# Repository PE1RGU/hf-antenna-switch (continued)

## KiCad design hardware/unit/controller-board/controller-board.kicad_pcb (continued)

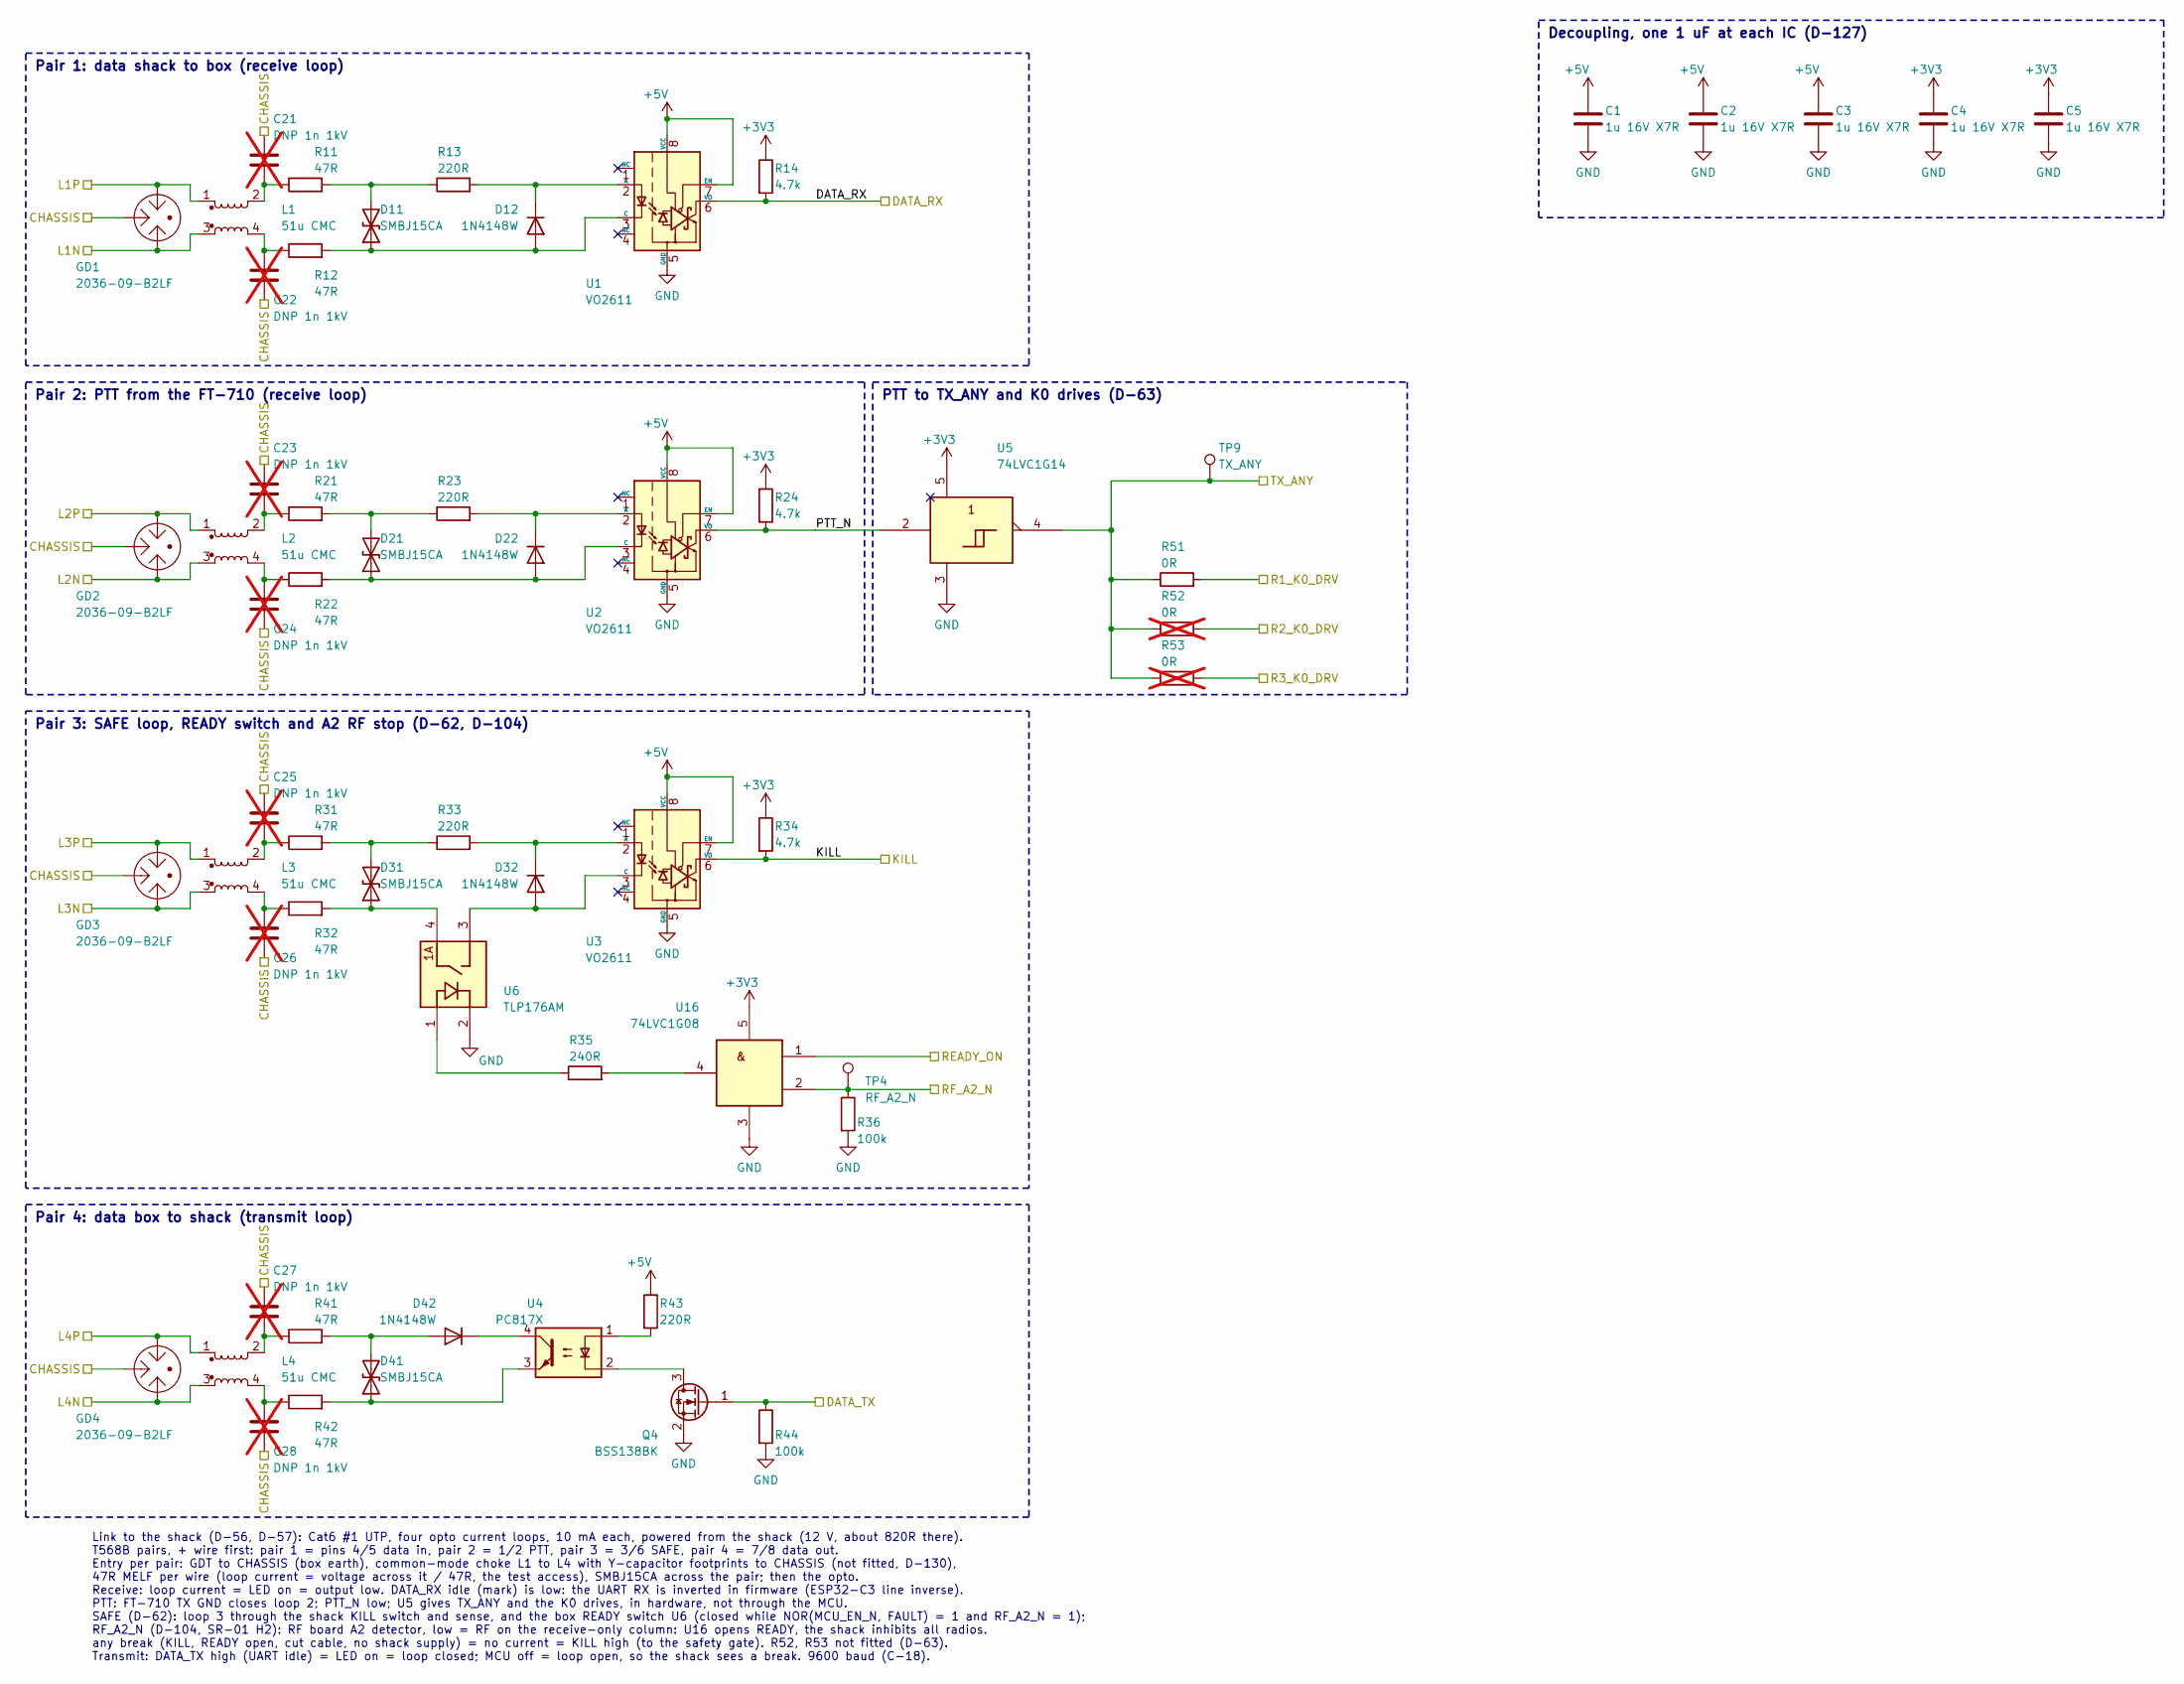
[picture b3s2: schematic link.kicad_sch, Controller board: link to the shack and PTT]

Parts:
C1, C2, C3, C4, C5: 1u 16V X7R; C_0603_1608Metric_Pad1.08x0.95mm_HandSolder
C21, C22, C23, C24, C25, C26, C27, C28: DNP 1n 1kV; C_1206_3216Metric_Pad1.33x1.80mm_HandSolder; not fitted
D11, D21, D31, D41: SMBJ15CA; D_SMB; MPN SMBJ15CA
D12, D22, D32, D42: 1N4148W; D_SOD-123; MPN 1N4148W
GD1, GD2, GD3, GD4: 2036-09-B2LF; GDT_3Pin_P4.40mm_Bourns-2036-B2_Littelfuse-SL1003A-R; MPN 2036-09-B2LF
L1, L2, L3, L4: 51u CMC; L_CMC_TDK_ACT45B; MPN ACT45B-510-2P-TL003
Q4: BSS138BK; SOT-23; MPN BSS138BK
R11, R12, R21, R22, R31, R32, R41, R42: 47R; R_MELF_MMB-0207
R13, R23, R33: 220R; R_MiniMELF_MMA-0204
R14, R24, R34: 4.7k; R_0603_1608Metric_Pad0.98x0.95mm_HandSolder
R35: 240R; R_0603_1608Metric_Pad0.98x0.95mm_HandSolder
R36, R44: 100k; R_0603_1608Metric_Pad0.98x0.95mm_HandSolder
R43: 220R; R_0603_1608Metric_Pad0.98x0.95mm_HandSolder
R51: 0R; R_0603_1608Metric_Pad0.98x0.95mm_HandSolder
R52, R53: 0R; R_0603_1608Metric_Pad0.98x0.95mm_HandSolder; not fitted
TP4: RF_A2_N; TestPoint_Pad_D1.5mm
TP9: TX_ANY; TestPoint_Pad_D1.5mm
U1, U2, U3: VO2611; DIP-8_W7.62mm; MPN VO2611
U4: PC817X; DIP-4_W7.62mm; MPN PC817X2NSZ9F
U5: 74LVC1G14; SOT-23-5; MPN 74LVC1G14GV
U6: TLP176AM; SOP-4_P2.54mm_PhotoRelay_LongPad; MPN TLP176AM(TPL,E)
U16: 74LVC1G08; SOT-23-5; MPN 74LVC1G08GV

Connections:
+3V3: C4.1, C5.1, R14.1, R24.1, R34.1, U5.5, U16.5; also elsewhere on the board
+5V: C1.1, C2.1, C3.1, R43.1, U1.7 (EN), U1.8 (VCC), U2.7 (EN), U2.8 (VCC), U3.7 (EN), U3.8 (VCC); also elsewhere on the board
/Link and PTT/CHASSIS: C21.1, C22.2, C23.1, C24.2, C25.1, C26.2, C27.1, C28.2, GD1.2, GD2.2, GD3.2, GD4.2; also elsewhere on the board
/Link and PTT/DATA_RX: R14.2, U1.6 (VO); also elsewhere on the board
/Link and PTT/KILL: R34.2, U3.6 (VO); also elsewhere on the board
/Link and PTT/L1N: GD1.1, L1.3; also elsewhere on the board
/Link and PTT/L1P: GD1.3, L1.1; also elsewhere on the board
/Link and PTT/L2N: GD2.1, L2.3; also elsewhere on the board
/Link and PTT/L2P: GD2.3, L2.1; also elsewhere on the board
/Link and PTT/L3N: GD3.1, L3.3; also elsewhere on the board
/Link and PTT/L3P: GD3.3, L3.1; also elsewhere on the board
/Link and PTT/L4N: GD4.1, L4.3; also elsewhere on the board
/Link and PTT/L4P: GD4.3, L4.1; also elsewhere on the board
/Link and PTT/PTT_N: R24.2, U2.6 (VO), U5.2
/Link and PTT/R1_K0_DRV: R51.2; also elsewhere on the board
/Link and PTT/R2_K0_DRV: R52.2; also elsewhere on the board
/Link and PTT/R3_K0_DRV: R53.2; also elsewhere on the board
/Link and PTT/READY_ON: U16.1; also elsewhere on the board
/Link and PTT/RF_A2_N: R36.1, TP4.1, U16.2; also elsewhere on the board
/Link and PTT/TX_ANY: R51.1, R52.1, R53.1, TP9.1, U5.4; also elsewhere on the board
/MCU and safety gate/DATA_TX: Q4.1 (G), R44.1; also elsewhere on the board
GND: C1.2, C2.2, C3.2, C4.2, C5.2, Q4.2 (S), R36.2, R44.2, U1.5 (GND), U2.5 (GND), U3.5 (GND), U5.3, U6.2, U16.3; also elsewhere on the board
unnamed: C21.2, L1.2, R11.1
unnamed: C22.1, L1.4, R12.1
unnamed: C23.2, L2.2, R21.1
unnamed: C24.1, L2.4, R22.1
unnamed: C25.2, L3.2, R31.1
unnamed: C26.1, L3.4, R32.1
unnamed: C27.2, L4.2, R41.1
unnamed: C28.1, L4.4, R42.1
unnamed: D11.1 (A1), D12.2 (A), R12.2, U1.3 (C)
unnamed: D11.2 (A2), R11.2, R13.1
unnamed: D12.1 (K), R13.2, U1.2 (A)
unnamed: D21.1 (A1), D22.2 (A), R22.2, U2.3 (C)
unnamed: D21.2 (A2), R21.2, R23.1
unnamed: D22.1 (K), R23.2, U2.2 (A)
unnamed: D31.1 (A1), R32.2, U6.4
unnamed: D31.2 (A2), R31.2, R33.1
unnamed: D32.2 (A), U3.3 (C), U6.3
unnamed: D32.1 (K), R33.2, U3.2 (A)
unnamed: D41.1 (A1), R42.2, U4.3
unnamed: D41.2 (A2), D42.2 (A), R41.2
unnamed: D42.1 (K), U4.4
unnamed: Q4.3 (D), U4.2
unnamed: R35.1, U6.1
unnamed: R35.2, U16.4
unnamed: R43.2, U4.1

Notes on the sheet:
Link to the shack (D-56, D-57): Cat6 #1 UTP, four opto current loops, 10 mA each, powered from the shack (12 V, about 820R there). T568B pairs, + wire first: pair 1 = pins 4/5 data in, pair 2 = 1/2 PTT, pair 3 = 3/6 SAFE, pair 4 = 7/8 data out. Entry per pair: GDT to CHASSIS (box earth), common-mod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
Pair 1: data shack to box (receive loop)
Pair 2: PTT from the FT-710 (receive loop)
PTT to TX_ANY and K0 drives (D-63)
Pair 3: SAFE loop, READY switch and A2 RF stop (D-62, D-104)
Pair 4: data box to shack (transmit loop)
Decoupling, one 1 uF at each IC (D-127)

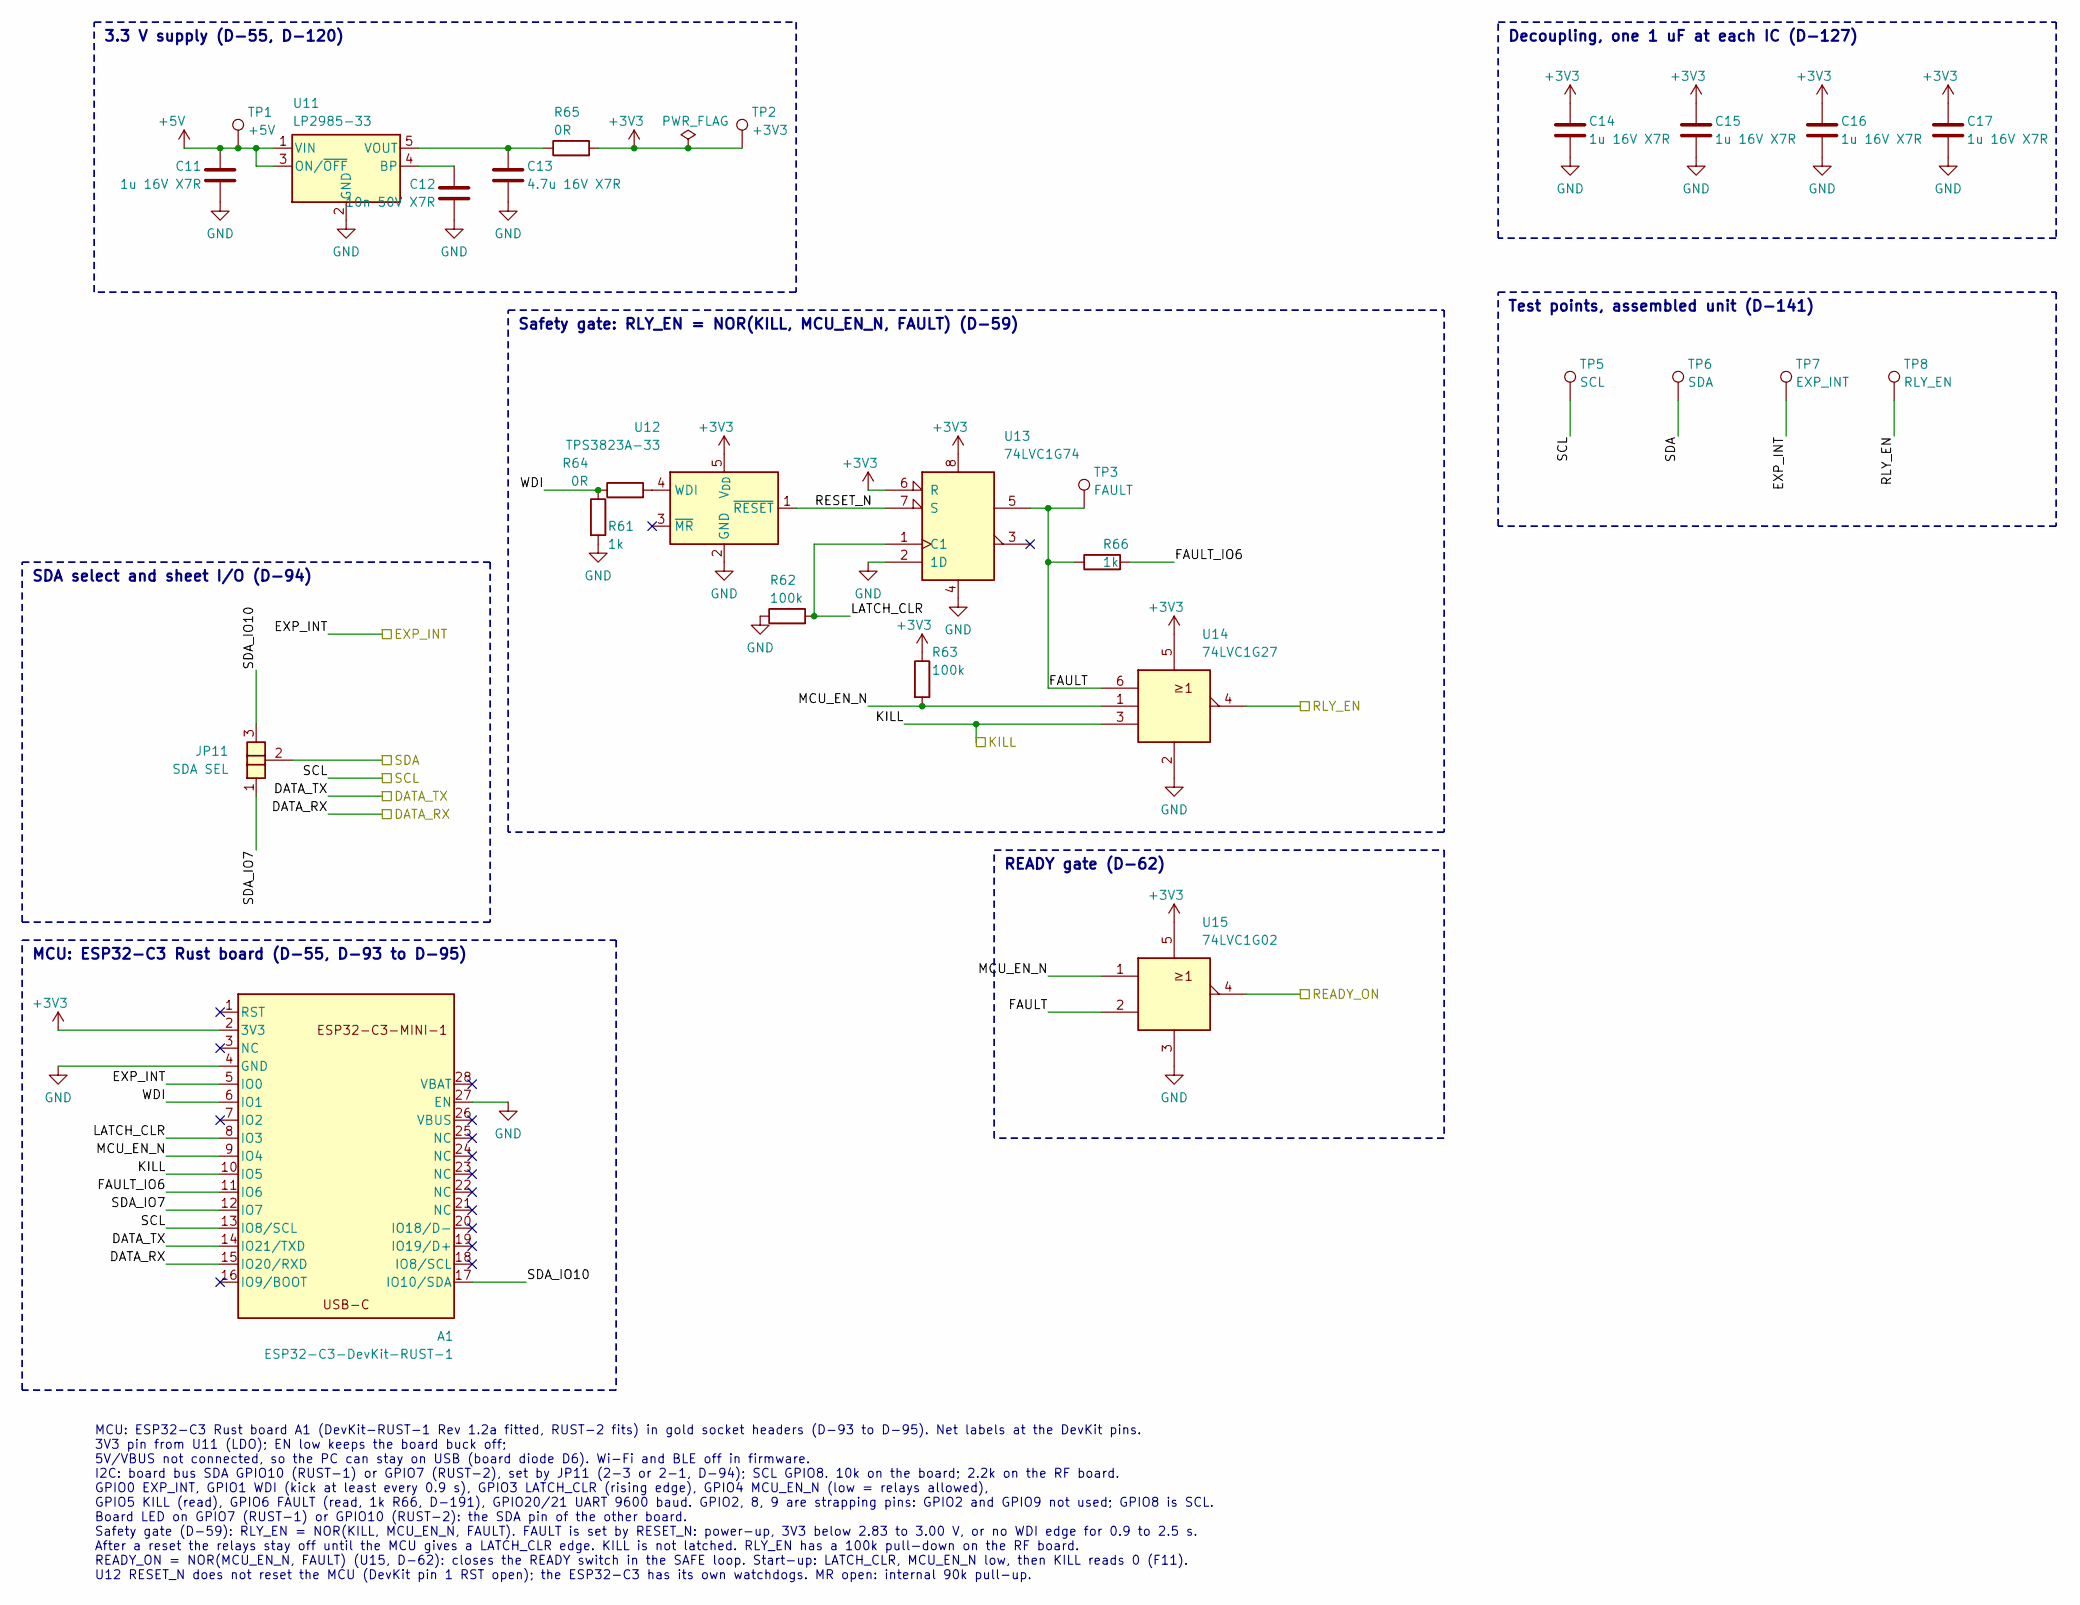
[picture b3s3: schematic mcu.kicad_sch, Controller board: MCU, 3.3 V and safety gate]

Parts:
A1: ESP32-C3-DevKit-RUST-1; ESP32-C3-DevKit-RUST_Socket
C11, C14, C15, C16, C17: 1u 16V X7R; C_0603_1608Metric_Pad1.08x0.95mm_HandSolder
C12: 10n 50V X7R; C_0603_1608Metric_Pad1.08x0.95mm_HandSolder
C13: 4.7u 16V X7R; C_0805_2012Metric_Pad1.18x1.45mm_HandSolder
JP11: SDA SEL; SolderJumper-3_P1.3mm_Open_RoundedPad1.0x1.5mm_NumberLabels
R61, R66: 1k; R_0603_1608Metric_Pad0.98x0.95mm_HandSolder
R62, R63: 100k; R_0603_1608Metric_Pad0.98x0.95mm_HandSolder
R64: 0R; R_0603_1608Metric_Pad0.98x0.95mm_HandSolder
R65: 0R; R_1206_3216Metric_Pad1.30x1.75mm_HandSolder
TP1: +5V; TestPoint_Pad_D1.5mm
TP2: +3V3; TestPoint_Pad_D1.5mm
TP3: FAULT; TestPoint_Pad_D1.5mm
TP5: SCL; TestPoint_Pad_D1.5mm
TP6: SDA; TestPoint_Pad_D1.5mm
TP7: EXP_INT; TestPoint_Pad_D1.5mm
TP8: RLY_EN; TestPoint_Pad_D1.5mm
U11: LP2985-33; SOT-23-5; MPN LP2985-33DBVR
U12: TPS3823A-33; SOT-23-5; MPN TPS3823A-33DBVR
U13: 74LVC1G74; VSSOP-8_2.3x2mm_P0.5mm; MPN SN74LVC1G74DCUR
U14: 74LVC1G27; SOT-23-6; MPN SN74LVC1G27DBVR
U15: 74LVC1G02; SOT-23-5; MPN 74LVC1G02GV

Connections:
+3V3: A1.2 (3V3), C14.1, C15.1, C16.1, C17.1, R63.1, R65.2, TP2.1, U12.5 (V_{DD}), U13.6 (R), U13.8, U14.5, U15.5; also elsewhere on the board
+5V: C11.1, TP1.1, U11.1 (VIN), U11.3 (ON/~OFF); also elsewhere on the board
/Link and PTT/DATA_RX: A1.15 (IO20/RXD); also elsewhere on the board
/Link and PTT/KILL: A1.10 (IO5), U14.3; also elsewhere on the board
/Link and PTT/READY_ON: U15.4; also elsewhere on the board
/MCU and safety gate/DATA_TX: A1.14 (IO21/TXD); also elsewhere on the board
/MCU and safety gate/EXP_INT: A1.5 (IO0), TP7.1; also elsewhere on the board
/MCU and safety gate/FAULT: R66.1, TP3.1, U13.5, U14.6, U15.2
/MCU and safety gate/FAULT_IO6: A1.11 (IO6), R66.2
/MCU and safety gate/LATCH_CLR: A1.8 (IO3), R62.2, U13.1 (C1)
/MCU and safety gate/MCU_EN_N: A1.9 (IO4), R63.2, U14.1, U15.1
/MCU and safety gate/RESET_N: U12.1 (~RESET), U13.7 (S)
/MCU and safety gate/RLY_EN: TP8.1, U14.4; also elsewhere on the board
/MCU and safety gate/SCL: A1.13 (IO8/SCL), TP5.1; also elsewhere on the board
/MCU and safety gate/SDA: JP11.2, TP6.1; also elsewhere on the board
/MCU and safety gate/WDI: A1.6 (IO1), R61.1, R64.1
GND: A1.4 (GND), A1.27 (EN), C11.2, C12.2, C13.2, C14.2, C15.2, C16.2, C17.2, R61.2, R62.1, U11.2 (GND), U12.2 (GND), U13.2 (1D), U13.4, U14.2, U15.3; also elsewhere on the board
unnamed: C12.1, U11.4 (BP)
unnamed: C13.1, R65.1, U11.5 (VOUT)
unnamed: R64.2, U12.4 (WDI)

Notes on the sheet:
MCU: ESP32-C3 Rust board A1 (DevKit-RUST-1 Rev 1.2a fitted, RUST-2 fits) in gold socket headers (D-93 to D-95). Net labels at the DevKit pins. 3V3 pin from U11 (LDO); EN low keeps the board buck off; 5V/VBUS not connected, so the PC can stay on USB (board diode D6). Wi-Fi and BLE off in firmware. I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
3.3 V supply (D-55, D-120)
SDA select and sheet I/O (D-94)
MCU: ESP32-C3 Rust board (D-55, D-93 to D-95)
Safety gate: RLY_EN = NOR(KILL, MCU_EN_N, FAULT) (D-59)
READY gate (D-62)
Decoupling, one 1 uF at each IC (D-127)
Test points, assembled unit (D-141)

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
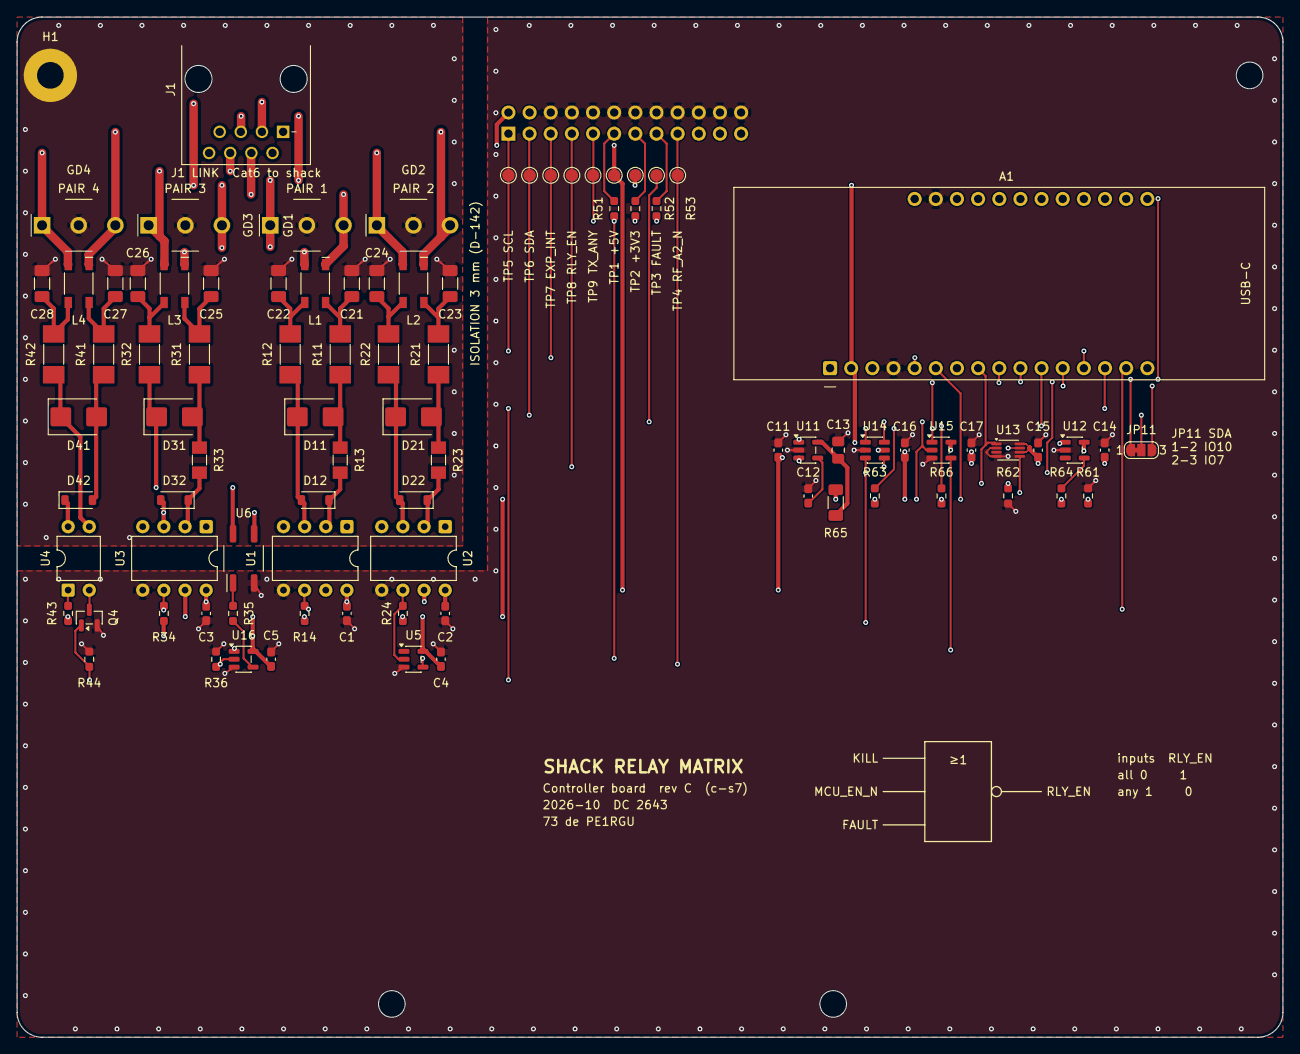
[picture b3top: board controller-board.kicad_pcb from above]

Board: 4 copper layers, 152.0 x 122.5 mm, 93 parts (1 on the bottom side), 62 nets.

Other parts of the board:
H2, H3, H4: M3 NPTH; MountingHole_3.2mm_M3

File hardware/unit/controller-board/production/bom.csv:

Designator,Footprint,Quantity,Value,LCSC Part #
A1,ESP32-C3-DevKit-RUST_Socket,1,ESP32-C3-DevKit-RUST-1,
"C1, C11, C14, C15, C16, C17, C2, C3, C4, C5",0603,10,1u 16V X7R,
C12,0603,1,10n,
C13,0805,1,4.7u 16V X7R,
"D11, D21, D31, D41",D_SMB,4,SMBJ15CA,
"D12, D22, D32, D42",D_SOD-123,4,1N4148W,
"GD1, GD2, GD3, GD4",GDT_3Pin_P4.40mm_Bourns-2036-B2_Littelfuse-SL1003A-R,4,2036-09-B2LF,
J1,RJ45_8P8C_Unshielded_TabDown,1,RJ45 LINK,
J2,PinSocket_2x12_P2.54mm_Vertical,1,to RF board J14,
JP11,SolderJumper-3_P1.3mm_Open_RoundedPad1.0x1.5mm_NumberLabels,1,SDA SEL,
"L1, L2, L3, L4",L_CMC_TDK_ACT45B,4,51u CMC,
Q4,SOT-23,1,BSS138BK,
"R11, R12, R21, R22, R31, R32, R41, R42",R_MELF_MMB-0207,8,47R,
"R13, R23, R33",R_MiniMELF_MMA-0204,3,220R,
"R14, R24, R34",0603,3,4.7k,
R35,0603,1,240R,
"R36, R44, R62, R63",0603,4,100k,
R43,0603,1,220R,
"R51, R64",0603,2,0R,
R61,0603,1,1k,
R65,1206,1,0R,
"U1, U2, U3",DIP-8_W7.62mm,3,VO2611,
U11,SOT-23-5,1,LP2985-33,
U12,SOT-23-5,1,TPS3823A-33,
U13,VSSOP-8_2.3x2mm_P0.5mm,1,74LVC1G74,
U14,SOT-23-6,1,74LVC1G27,
U15,SOT-23-5,1,74LVC1G02,
U16,SOT-23-5,1,74LVC1G08,
U4,DIP-4_W7.62mm,1,PC817X,
U5,SOT-23-5,1,74LVC1G14,
U6,SOP-4_P2.54mm_PhotoRelay_LongPad,1,TLP176AM,

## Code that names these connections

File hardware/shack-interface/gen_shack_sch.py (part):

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_g = open("_sym/power__GND.sym").read().strip()
_g = _g.replace('(symbol "GND"', '(symbol "shack-interface:CHASSIS"', 1).replace('(property "Value" "GND"', '(property "Value" "CHASSIS"')
_g = _g.replace('"GND_0_1"', '"CHASSIS_0_1"').replace('"GND_1_1"', '"CHASSIS_1_1"')
_g = _g.replace('Power symbol creates a global label with name \\"GND\\" , ground', 'Chassis (frame) connection, IEC 60417-5020')
_poly = lambda pts: ('\t\t\t(polyline\n\t\t\t\t(pts\n\t\t\t\t\t' + " ".join(f"(xy {x} {y})" for x, y in pts) +
                     '\n\t\t\t\t)\n\t\t\t\t(stroke\n\t\t\t\t\t(width 0)\n\t\t\t\t\t(type default)\n\t\t\t\t)\n\t\t\t\t(fill\n\t\t\t\t\t(type none)\n\t\t\t\t)\n\t\t\t)\n')
_i = _g.index('(symbol "CHASSIS_0_1"'); _j = _g.index('(symbol "CHASSIS_1_1"')
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_r = open("_sym/power__GND.sym").read().strip()
_r = _r.replace('(symbol "GND"', '(symbol "shack-interface:RGND"', 1).replace('(property "Value" "GND"', '(property "Value" "RGND"')
_r = _r.replace('"GND_0_1"', '"RGND_0_1"').replace('"GND_1_1"', '"RGND_1_1"').replace("(power global)", "(power local)")
_r = _r.replace('Power symbol creates a global label with name \\"GND\\" , ground', 'Radio GND of one port: local net, one per sheet instance (floating port)')
_r = _r.replace("(type none)", "(type outline)", 1)        # filled triangle: radio GND, apart from the hollow GND triangle
assert "(power local)" in _r and "RGND_1_1" in _r
SYMS["shack-interface:RGND"] = _r
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LOOPS = [(1, (4, 5), "DATA_TX", "down", None),          # data shack to box: source switched by the UART
         (2, (1, 2), "R1_TX", "down", None),            # PTT to R1 K0: source switched by R1 TX sense, in hardware
         (3, (3, 6), "SW_STOP_N", "up", "SAFE_LOST"),   # SAFE: KILL switch in series, software stop, sensed
         (4, (7, 8), None, None, "DATA_RX")]            # data box to shack: box PC817 switches, sensed
BAND = 63.5

def shack_entry(S, k, yp):
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    YP = S.part("Device:C", ("C", 20 + 2 * k), "DNP 1n 1kV", "Capacitor_SMD:C_1206_3216Metric_Pad1.33x1.80mm_HandSolder", 143.51, R2(yp - 3.81), dnp=True,
                rp=(1.27, -6.35), desc="P wire to CHASSIS behind the choke, footprint only: fit on the bench if the loops pick up HF (D-130)")
    assert YP["2"] == (143.51, yp), YP
    S.label("H", "CHASSIS", 143.51, R2(yp - 7.62), 90)
    YN = S.part("Device:C", ("C", 21 + 2 * k), "DNP 1n 1kV", "Capacitor_SMD:C_1206_3216Metric_Pad1.33x1.80mm_HandSolder", 143.51, R2(yn + 3.81), dnp=True,
                rp=(1.27, 3.81), desc="N wire to CHASSIS behind the choke, footprint only (D-130)")
    assert YN["1"] == (143.51, yn), YN
    S.label("H", "CHASSIS", 143.51, R2(yn + 7.62), 270)
    S.wire(G["2"], (R2(XG + 10.16), R2(yp + 5.08))); S.label("H", "CHASSIS", R2(XG + 10.16), R2(yp + 5.08), 0)
    assert T["1"] == RN["1"], (T, RN)                        # TVS on the R pins
    return (XT, yp), (XT, yn)

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        S.power("GND", RG["2"])
    else:
        RG = S.part("Device:R", ("R", n + 5), "100k", R0603, xp, R2(g[1] - 3.81), rp=(1.27, -1.27),
                    desc="Gate pull-up: SAFE source on while the expander pin is an input (power-up, reset). SW_STOP_N low opens the loop")
        S.power("+3V3", RG["1"])
    return Q1["2"]

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        (xp, _), (xn, yn) = shack_entry(S, k, yp)
        if k == 3:                                      # KILL switch in series with the SAFE loop, on the front panel
            Y1, Y2 = R2(y0 - 12.7), R2(y0 - 7.62)                # KILL switch wires out on the cable side, like the root block
            S.wire(c, (111.76, yp), (111.76, Y1), (172.72, Y1)); S.label("H", "KILL_1", 172.72, Y1, 0)
            S.wire((172.72, Y2), (119.38, Y2), (119.38, yp), (xp, yp)); S.label("H", "KILL_2", 172.72, Y2, 0)
        else:
            S.wire(c, (xp, yp))
        if sense:
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           "Loop 2: R1_TX (FT-710 TX GND through the R1 TX sense) switches the source in hardware: PTT to R1 K0 without the MCU.\\n"
           "Loop 3 SAFE: KILL switch in series (front panel); SW_STOP_N low turns the source off (software stop).\\n"
           "The box READY switch closes the loop (D-62). SAFE_LOST high = no loop current (to the SAFE latch).\\n"
           "Loop 4: the box PC817 switches the current; DATA_RX low = current (inverted UART).\\n"
           "Drawn with the cable side on the left and the logic side on the right, as the block on the root sheet.", 218.44, 25.4)
    return S.finish()

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    S = Sheet("Shack interface: power 13.8 V, 5 V, 3.3 V", "A3", [(PATH["power"], 0)], pwr_base=[300])
    Y = 50.8
    cap = lambda ref, val, fp, x, desc, lib="Device:C": S.part(lib, ("C", ref), val, fp, x, R2(Y + 3.81), rp=(1.27, 1.27), desc=desc)
    S.wire((25.4, Y), (34.29, Y)); S.label("H", "VIN_P", 25.4, Y, 180)
    F = S.part("Device:Fuse", ("F", 1), "500mA T", "Fuse:Fuse_1206_3216Metric", 38.1, Y, rot=90, rp=(-2.54, -5.08), mpn="SF-1206S050",
               desc="Input fuse, slow, 500 mA (budget C-25: about 0.2 A). Bourns SF-1206S class (as the box); part to confirm")
    D = S.part("Device:D_Schottky", ("D", 1), "SS34", "Diode_SMD:D_SMC", 53.34, Y, rot=180, rp=(-2.54, -5.08), mpn="SS34-M3/57T",
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           "Exceptions (D-124): SMBJ16A at 15 V max (0.94); L7805 capacitors 330 nF in, 100 nF out per the ST datasheet.", 25.4, 88.9)
    return S.finish()

# PCA9539 0x74 pin map (D-92): IO0_0..1 to the left edge, IO0_2..IO1_5 to the bottom edge (port group, root order),
# IO1_6..7 under the chip to the right edge. Directions per bit in firmware; F1 unchanged.
EXP = ["SW_STOP_N", "R1_TX", "KEY_R1", "BAND_D", "BAND_A", "BAND_B", "BAND_C", "DISP_BL",
       "KEY_R2", "R2_TX", "DISP_DC", "KEY_R3", "R3_TX", "DISP_RST", "KILL_S", "LATCHED"]      # IO0_0..7, IO1_0..7 (D-180: LED_R1..R3 -> display)
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        elif n == 2: S.wire((x, y), (60.96, y)); S.power("+3V3", (60.96, y), rot=90, rp=(-5.08, -2.54, "right"))
        elif n == 4: S.wire((x, y), (60.96, y)); S.power("GND", (60.96, y), rot=270, rp=(-5.08, -2.54, "right"))
        elif n == 27: S.wire((x, y), (124.46, y)); S.power("GND", (124.46, y))      # EN low: board buck off
        elif n == 17: S.wire((x, y), (127.0, y)); S.label("L", "SDA_IO10", 127.0, y, 0)   # SDA on RUST-1
        elif n in (19, 20): S.wire((x, y), (127.0, y)); S.label("L", {19: "USB_DP", 20: "USB_DN"}[n], 127.0, y, 0)   # to J14 (D-96)
        elif n != 14: NC((x, y))
    y = A1["14"][1]
    RS = S.part("Device:R", ("R", 61), "1k", R0603, 59.69, y, rot=90,
                desc="Series resistor: IO21 is the boot-ROM UART TX; limits the current into the loop 3 sense transistor during boot")
    assert RS["2"] == (63.5, y) and RS["1"] == (55.88, y), RS
    S.wire(A1["14"], RS["2"]); S.wire(RS["1"], (50.8, y)); S.label("L", "SAFE_LOST", 50.8, y, 180)
    # ---- left edge (root block order): SAFE_LOST, DATA_TX, SW_STOP_N, DATA_RX, R1_TX ----
    for nm, yy in (("SAFE_LOST", 109.22), ("DATA_TX", 114.3), ("DATA_RX", 124.46)):
        S.wire((XL, yy), (43.18, yy)); S.label("H", nm, XL, yy, 180); S.label("L", nm, 43.18, yy, 0)
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    assert U3["4"] == (259.08, 63.5) and U3["1"] == (279.4, 66.04) and U3["3"] == (259.08, 68.58), U3
    RW = S.part("Device:R", ("R", 62), "1k", R0603, 251.46, 67.31, rp=(1.27, 1.27),
                desc="WDI pull-down: a floating WDI would disable the watchdog (MAX823 WDI pin; TPS3823 7.3.4). MAX823 WDI sources max 20 uA: 20 mV low")
    assert RW["1"] == (251.46, 63.5), RW
    S.wire((246.38, 63.5), RW["1"], U3["4"]); S.label("L", "WDI", 246.38, 63.5, 180); S.power("GND", RW["2"])
    NC(U3["3"]); S.power("+3V3", U3["5"]); S.power("GND", U3["2"])
    U4 = S.part("shack-interface:74LVC1G74_IEC", ("U", 4), "74LVC1G74", "Package_SO:VSSOP-8_2.3x2mm_P0.5mm", 304.8, 68.58,
                mpn="SN74LVC1G74DCUR", rp=(6.35, -12.7),
                desc="D flip-flop, fault latch: D = GND, CLR_N = 3V3, PRE_N = RESET_N (TI SCES794G, DCU VSSOP-8, D-190 as D-154). Second source Nexperia 74LVC1G74DC,125 (SOT765-1, same pin-out and MO-187 land)")
    assert U4["7"] == (294.64, 66.04) and U4["6"] == (294.64, 63.5) and U4["1"] == (294.64, 71.12) and U4["2"] == (294.64, 73.66), U4
    XR, XC = 281.94, 287.02
    S.wire(U3["1"], (XR, 66.04), U4["7"])
    S.wire(U4["6"], (292.1, 63.5)); S.power("+3V3", (292.1, 63.5))
    S.wire(U4["2"], (292.1, 73.66)); S.power("GND", (292.1, 73.66))
    NC(U4["3"]); S.power("+3V3", U4["8"]); S.power("GND", U4["4"])
    S.wire(U4["1"], (XC, 71.12), (XC, 88.9)); S.wire((XC, 88.9), (294.64, 88.9)); S.label("L", "LATCH_CLR", 294.64, 88.9, 0)
    RL = S.part("Device:R", ("R", 63), "100k", R0603, XC, 92.71, rp=(-1.27, 1.27, "right"),
                desc="LATCH_CLR pull-down: no clock edge while the MCU is in reset")
    assert RL["1"] == (XC, 88.9), RL
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    UE = S.part("shack-interface:USBLC6-2SC6", ("U", 61), "USBLC6-2SC6", "Package_TO_SOT_SMD:SOT-23-6", 360.68, 25.4, mpn="USBLC6-2SC6",
                rp=(-5.08, -10.16), desc="ESD protection for D+, D- and VBUS at J14 (ST USBLC6-2 DS4260 Rev 7). Second source UMW USBLC6-2SC6 (same pin-out). C-26")
    assert UE["1"] == (353.06, 22.86) and UE["6"] == (368.3, 22.86) and UE["3"] == (353.06, 27.94) and UE["5"] == (363.22, 33.02), UE
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
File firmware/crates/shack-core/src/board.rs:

//! Shack interface pin map, as drawn in hardware/shack-interface/gen_shack_sch.py.
//! Direct GPIO: D-83. PCA9539 map: D-92, display pins D-180. SDA select: D-94.
//!
//! The safety lines that must react fast (PERMIT, WDI, LATCH_CLR, SAFE_LOST) and
//! the box link are on direct ESP32-C3 GPIO. The slow lines (keys, TX sense, band
//! data, KILL, LATCHED, display control) are on the PCA9539 expander U5, which the
//! logic polls every tick (10 ms). The expander RESET is the supervisor RESET_N, so
//! a watchdog or brown-out reset sets all its pins back to inputs.

/// I2C address of the PCA9539 (U5).
pub const EXPANDER_ADDR: u8 = 0x74;

/// ESP32-C3 GPIO numbers of the direct lines (D-83, D-180).
pub mod gpio {
    /// IO0, output: PERMIT_R1. High = R1 may transmit (C-1).
    pub const PERMIT_R1: u8 = 0;
    /// IO1, output: supervisor watchdog input. Toggled every tick (D-59).
    pub const WDI: u8 = 1;
    /// IO2, output: display SPI clock (D-180). Strapping pin; the display input is
    /// high impedance, so the boot strap keeps its pull-up.
    pub const DISP_SCK: u8 = 2;
    /// IO3, output: fault latch clear. One rising edge after start-up (D-59).
    pub const LATCH_CLR: u8 = 3;
    /// IO4, output: PERMIT_R2. High only while the box reports the permit (D-63).
    pub const PERMIT_R2: u8 = 4;
    /// IO5, output: PERMIT_R3. High only while the box reports the permit (D-63).
    pub const PERMIT_R3: u8 = 5;
    /// IO6, output: UART TX of the box link (9600 8N1).
    pub const DATA_TX: u8 = 6;
    /// IO8: I2C clock to the PCA9539 (both DevKit revisions).
    pub const SCL: u8 = 8;
    /// IO9, output: display SPI data (D-180). Strapping pin (BOOT).
    pub const DISP_MOSI: u8 = 9;
    /// IO20, input: UART RX of the box link.
    pub const DATA_RX: u8 = 20;
    /// IO21, input: high = no SAFE loop current. 1k series resistor against the
    /// boot-ROM log.
    pub const SAFE_LOST: u8 = 21;
}

/// DevKit board revision. It sets the SDA pin (JP61, D-94) and the board LED.
#[derive(Clone, Copy, Debug, PartialEq, Eq)]
pub enum DevKit {
    /// ESP32-C3-DevKit-RUST-1: SDA on GPIO10, LED on GPIO7. JP61 as delivered (1-2 bridged by copper, D-192).
    Rust1,
    /// ESP32-C3-DevKit-RUST-2: SDA on GPIO7, LED on GPIO10. JP61: cut 1-2, bridge 2-3.
    Rust2,
}

impl DevKit {
    /// GPIO number of the I2C data line on this revision.
    pub const fn sda(self) -> u8 {
        match self {
            DevKit::Rust1 => 10,
            DevKit::Rust2 => 7,
        }
    }

    /// The board LED sits on the SDA pin of the other revision.
    pub const fn led(self) -> u8 {
        match self {
            DevKit::Rust1 => 7,
            DevKit::Rust2 => 10,
        }
    }
}

/// One PCA9539 pin: bit 0..=15, IO0_0 = 0, IO1_7 = 15.
#[derive(Clone, Copy, Debug, PartialEq, Eq)]
pub struct ExpPin {
    /// Bit number in the 16-bit port word: port 0 is bits 0 to 7, port 1 is
    /// bits 8 to 15.
    pub bit: u8,
    /// `true` = output (configuration bit 0), `false` = input.
    pub output: bool,
    /// Net name in the schematic.
    pub name: &'static str,
}

const fn out(bit: u8, name: &'static str) -> ExpPin {
    ExpPin {
        bit,
        output: true,
        name,
    }
}

const fn inp(bit: u8, name: &'static str) -> ExpPin {
    ExpPin {
        bit,
        output: false,
        name,
    }
}

/// PCA9539 pins (D-92, D-180).
pub mod exp {
    use super::{ExpPin, inp, out};

    /// IO0_0, output: software stop, active low. Low opens the SAFE loop.
    pub const SW_STOP_N: ExpPin = out(0, "SW_STOP_N");
    /// IO0_1, input: R1 TX sense. High = R1 transmits.
    pub const R1_TX: ExpPin = inp(1, "R1_TX");
    /// IO0_2, output: key R1 through the interface. Gated by PERMIT_R1 in hardware.
    pub const KEY_R1: ExpPin = out(2, "KEY_R1");
    /// IO0_3, input: R1 band data, bit D (most significant).
    pub const BAND_D: ExpPin = inp(3, "BAND_D");
    /// IO0_4, input: R1 band data, bit A (least significant).
    pub const BAND_A: ExpPin = inp(4, "BAND_A");
    /// IO0_5, input: R1 band data, bit B.
    pub const BAND_B: ExpPin = inp(5, "BAND_B");
    /// IO0_6, input: R1 band data, bit C.
    pub const BAND_C: ExpPin = inp(6, "BAND_C");
    /// IO0_7, output: display backlight. High = on (D-180).
    pub const DISP_BL: ExpPin = out(7, "DISP_BL");
    /// IO1_0, output: key R2. Gated by PERMIT_R2 in hardware.
    pub const KEY_R2: ExpPin = out(8, "KEY_R2");
    /// IO1_1, input: R2 TX sense. High = R2 transmits.
    pub const R2_TX: ExpPin = inp(9, "R2_TX");
    /// IO1_2, output: display D/C. Low = command, high = data (D-180).
    pub const DISP_DC: ExpPin = out(10, "DISP_DC");
    /// IO1_3, output: key R3. Gated by PERMIT_R3 in hardware.
    pub const KEY_R3: ExpPin = out(11, "KEY_R3");
    /// IO1_4, input: R3 TX sense. High = R3 transmits.
    pub const R3_TX: ExpPin = inp(12, "R3_TX");
    /// IO1_5, output: display reset, active low (D-180).
    pub const DISP_RST: ExpPin = out(13, "DISP_RST");
    /// IO1_6, input: KILL switch state. High = KILL pressed.
    pub const KILL_S: ExpPin = inp(14, "KILL_S");
    /// IO1_7, input: SAFE latch state. High = latched (TX blocked until RESET).
    pub const LATCHED: ExpPin = inp(15, "LATCHED");

    /// All 16 pins in bit order. A test checks that each bit is used once.
    pub const ALL: [ExpPin; 16] = [
        SW_STOP_N, R1_TX, KEY_R1, BAND_D, BAND_A, BAND_B, BAND_C, DISP_BL, KEY_R2, R2_TX, DISP_DC,
        KEY_R3, R3_TX, DISP_RST, KILL_S, LATCHED,
    ];
}

/// PCA9539 configuration word (register 6 low byte, register 7 high byte):
/// 1 = input, 0 = output.
///
/// The value is computed from [`exp::ALL`] at compile time. The logic writes the
/// outputs first and this word second (F1), and it reads the word back every tick:
/// a different value means that the expander was reset.
///
/// ```
/// use shack_core::board::{exp, expander_config};
///
/// let cfg = expander_config();
/// assert_eq!(cfg & (1 << exp::KEY_R1.bit), 0, "KEY_R1 is an output");
/// assert_ne!(cfg & (1 << exp::LATCHED.bit), 0, "LATCHED is an input");
/// assert_eq!(cfg, 0b1101_0010_0111_1010);
/// ```
pub const fn expander_config() -> u16 {
    let mut cfg = 0xFFFF;
    let mut i = 0;
    while i < exp::ALL.len() {
        if exp::ALL[i].output {
            cfg &= !(1 << exp::ALL[i].bit);
        }
        i += 1;
    }
    cfg
}

#[cfg(test)]
mod tests {
    use super::*;

    #[test]
    fn every_expander_bit_used_once() {
        let mut seen = 0u16;
        for p in exp::ALL {
            assert!(p.bit < 16);
            assert_eq!(seen & (1 << p.bit), 0, "bit {} used twice", p.bit);
            seen |= 1 << p.bit;
        }
        assert_eq!(seen, 0xFFFF);
    }

    #[test]
    fn expander_config_matches_d92() {
        // Outputs: IO0_0, IO0_2, IO0_7, IO1_0, IO1_2, IO1_3, IO1_5.
        assert_eq!(expander_config(), 0b1101_0010_0111_1010);
    }

    #[test]
    fn devkit_sda_and_led_swap() {
        for kit in [DevKit::Rust1, DevKit::Rust2] {
            assert_ne!(kit.sda(), kit.led());
            assert_ne!(kit.sda(), gpio::SCL);
        }
        assert_eq!(DevKit::Rust1.sda(), DevKit::Rust2.led());
    }
}

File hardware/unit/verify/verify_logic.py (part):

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p("## 1. Topology checks against the netlists\n")
p("| Check | Result |\n|---|---|")
C = "/MCU and safety gate/"
check(members(ct_nets, C + "RLY_EN") == {("U14", "4"), ("J2", "7")}, "Controller: RLY_EN = U14 output to J2 pin 7 only")
check({("U14", "3")} <= members(ct_nets, "/Link and PTT/KILL") and {("U14", "1")} <= members(ct_nets, C + "MCU_EN_N")
      and members(ct_nets, C + "FAULT") == {("U13", "5"), ("U14", "6"), ("U15", "2"), ("R66", "1")}, "U14 NOR inputs: KILL (pin 3), MCU_EN_N (pin 1), FAULT = U13 Q (pin 6); FAULT also to the READY gate U15 (D-62) and to R66")
check(ct_parts["JP11"][1].endswith("SolderJumper_3_Bridged12") and ct_pin[("JP11", "1")] == C + "SDA_IO10"
      and ct_pin[("JP11", "3")] == C + "SDA_IO7" and ("A1", "17") in members(ct_nets, C + "SDA_IO10"),
      "SDA select JP11: pad 1 (bridged to 2 by copper) = SDA_IO10 = DevKit pad 17, the RUST-1 default the firmware uses (D-192)")
check(members(ct_nets, C + "FAULT_IO6") == {("R66", "2"), ("A1", "11")} and ct_parts["R66"][0] == "1k",
      "FAULT read-back: R66 1k from FAULT to DevKit pin 11 (GPIO6), input only (D-191)")
check(members(ct_nets, C + "RESET_N") == {("U12", "1"), ("U13", "7")}, "U13 PRE_N (pin 7) = U12 RESET_N only")
check(ct_pin[("U13", "2")] == "GND" and ct_pin[("U13", "6")] == "+3V3", "U13 D (pin 2) = GND, CLR_N (pin 6) = +3V3")
check({("U13", "1"), ("R62", "2")} <= members(ct_nets, C + "LATCH_CLR") and ct_pin[("R62", "1")] == "GND", "LATCH_CLR = U13 CLK, R62 100k pull-down")
check(ct_pin[("R63", "1")] == "+3V3" and ct_parts["R63"][0] == "100k", "MCU_EN_N: R63 100k pull-up to +3V3")
check({("U12", "4"), ("R61", "1")} <= members(ct_nets, C + "WDI") and ct_pin[("R61", "2")] == "GND" and ct_parts["R61"][0] == "1k",
      "WDI: R61 1k to GND (floating WDI would disable the watchdog)")
check(ct_parts["U12"][0] == "TPS3823A-33" and ct_pin.get(("U12", "3")) is not None and len(ct_nets[ct_pin[("U12", "3")]]) == 1,
      "U12 TPS3823A-33, MR (pin 3) open (internal 90k pull-up)")
check(members(ct_nets, "/Link and PTT/KILL") >= {("U3", "6"), ("R34", "2")} and ct_pin[("R34", "1")] == "+3V3",
      "KILL = U3 opto output (loop 3) with R34 pull-up: loop open = KILL high")
check(members(ct_nets, "/Link and PTT/PTT_N") >= {("U2", "6"), ("U5", "2"), ("R24", "2")} and ct_pin[("R24", "1")] == "+3V3",
      "PTT_N = U2 opto output (loop 2), R24 pull-up, into U5 (Schmitt inverter)")
check(all(ct_pin[(f"R5{i}", "1")] == "/Link and PTT/TX_ANY" and ct_pin[(f"R5{i}", "2")] == f"/Link and PTT/R{i}_K0_DRV" for i in (1, 2, 3)),
      "TX_ANY (U5 out) to R1..R3_K0_DRV through the 0R footprints R51..R53")
check("R51" not in ct_dnp and {"R52", "R53"} <= ct_dnp, "R51 fitted (R1 K0 follows PTT); R52, R53 not fitted: R2, R3 K0 come from U903 (D-63)")
for pin_, nm in ((7, "RLY_EN"), (9, "TX_ANY"), (11, "R1_K0_DRV"), (13, "R2_K0_DRV"), (15, "R3_K0_DRV")):
    check(ct_pin[("J2", str(pin_))].endswith(nm) and rf_pin[("J14", str(pin_))].endswith(nm), f"J2 / J14 pin {pin_} = {nm} on both boards")
check(members(rf_nets, "/RLY_EN") == {("J14", "7"), ("R3", "1"), ("Q2", "1"), ("U901", "3"), ("U902", "3"), ("U903", "3"), ("U1001", "3")}
      and rf_pin[("R3", "2")] == "GND", "RF board: RLY_EN = R3 100k pull-down, Q2 gate, RESET of U901, U902, U903, U1001")
check(rf_pin[("Q2", "2")] == "GND" and rf_pin[("R2", "2")] == rf_pin[("Q2", "3")] and rf_pin[("R2", "1")] == rf_pin[("Q1", "1")]
      and rf_pin[("R1", "1")] == "+12V_RLY" and rf_pin[("Q1", "2")] == "+12V_RLY" and rf_pin[("Q1", "3")] == "+12V_SW",
      "+12V_SW switch: Q2 (RLY_EN) pulls Q1 gate low through R2; R1 holds Q1 off")
check(rf_pin[("J14", "17")] == rf_pin[("U901", "18")] and rf_pin[("J14", "17")].endswith("A2_RFDET")
      and ct_pin[("J2", "17")].endswith("RF_A2_N") and ("U16", "2") in members(ct_nets, ct_pin[("J2", "17")]),
      "J14 / J2 pin 17: RF board A2 detector output (A2_RFDET, also U901 input) to the controller READY gate U16 (D-104, SR-01 H2)")
# SR-01 (D-103): receive-only column A2 has no TX relay and no TX coil driver, in all three radios
_tx2 = {f"{x}{100 * i + 3}" for i in (1, 2, 3) for x in "KQDR"}
_rows = {f"K{100 * i + k}" for i in (1, 2, 3) for k in range(2, 12)}
check(all(rf_parts[f"K{100 * i + 3}"][0] == "RTD14012F" and rf_pin[(f"K{100 * i + 3}", "14")] == "/ANT2" for i in (1, 2, 3))
      and _tx2 <= rf_dnp and not ((_rows - {f"K{100 * i + 3}" for i in (1, 2, 3)}) & rf_dnp),
      "SR-01: TX relays at A2 (K103, K203, K303) and their drivers Q, D, R not fitted; all other row relays fitted (D-103)")
# relays and drivers
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      "K0 gates on J14 and U903: IO1_2 reads R1 K0 (driven from TX_ANY through R51); IO1_3, IO1_4 drive R2, R3 K0 (R52, R53 open, D-63)")
check(all(len(drive[k][2]) == 1 and drive[k][2][0][0] in ("U901", "U902", "U903") for k in relays if k not in k0),
      "Every other coil gate is driven by exactly one PCA9539 pin")
check(rf_pin[("K101", "11")] == "/R1_RADIO" and rf_pin[("K101", "12")].endswith("RXBUS") and rf_pin[("K101", "14")].endswith("TXBUS"),
      "K0: COM (11) radio, NC (12) RX row, NO (14) TX row: coil off = receive")
check(members(rf_nets, "/TX_ANY") == {("J14", "9"), ("U903", "18"), ("R904", "1")} and rf_pin[("R904", "2")] == "GND"
      and rf_parts["R904"][0] == "100k", "RF board TX_ANY: J14 pin 9, U903 IO1_5, R904 100k pull-down (F4, D-61)")
p("")

# ---------------------------------------------------------------- 2. combinational tables
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check_safe(lambda: all(rf_raw_parts[c][0] == "1u 50V X7R" and {rf_raw_pin[(c, "1")], rf_raw_pin[(c, "2")]} == {"+12V_SW", "GND"} for c in ("C101", "C201", "C301")), "+12V_SW: 1 uF 50 V X7R at each radio block (C101, C201, C301) (D-127)")
check_safe(lambda: all(rf_raw_parts[c][0] == "1u 16V X7R" for c in ("C901", "C902", "C903", "C1001", "C802")), "IC decoupling one value: 1 uF X7R at U901 to U903, U1001, U801 (D-127)")
check_safe(lambda: all(rf_raw_parts[u][0] == "PCA9539" for u in ("U901", "U902", "U903", "U1001")), "Expanders U901 to U903, U1001 = PCA9539 (TSSOP-24, three makers, D-133)")
check_safe(lambda: rf_raw_pin[("H1", "1")].endswith("/CHASSIS")
           and all(rf_raw_pin[(f"S{i}", "1")].endswith(f"/CHASSIS_S{i}") and f"C{7 + i}" in rf_dnp
                   and {(r, q) for r, q, _ in rf_raw_nets[rf_raw_pin[(f"S{i}", "1")]]} == {(f"S{i}", "1"), (f"C{7 + i}", "1")}
                   and rf_raw_pin[(f"C{7 + i}", "2")] == "GND" for i in range(1, 7)),
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           "Controller: Y-capacitor footprints C21 to C28 (DNP) from each wire behind the choke to CHASSIS (D-130)")
check_safe(lambda: ct_raw_parts["R64"][0] == "0R" and cpn("R64", "2") == cpn("U12", "4") and cpn("R64", "1") == cpn("R61", "1")
           and cpn("R61", "1") != cpn("U12", "4") and len(cmem(cpn("U12", "4"))) == 2,
           "Controller: watchdog link R64 0R between WDI (GPIO1, R61) and U12 WDI; open = WDI floats = watchdog off (D-123)")
check_safe(lambda: ct_raw_parts["R65"][0] == "0R" and {cpn("R65", "1"), cpn("R65", "2")} == {cpn("U11", "5"), "+3V3"}, "Controller: +3V3 current link R65 0R after U11 (D-120)")
ctp = {cpn(r, "1") for r in ct_raw_parts if r.startswith("TP")}
check_safe(lambda: {"+5V", "+3V3"} <= ctp and any(n.endswith("/FAULT") for n in ctp) and any(n.endswith("RF_A2_N") for n in ctp),
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
p("## 3. Input states that are not a clean 0 or 1 (open pins, missing parts)\n")
p("| Case | Net state | Result at the gate | RLY_EN |\n|---|---|---|---|")
cases = [("MCU not fitted or in reset (GPIO high-Z)", "MCU_EN_N Z, pulled to 1 by R63; LATCH_CLR Z, pulled to 0; WDI Z, pulled to 0",
          "MCU_EN_N = 1; WDI static low: watchdog trips, FAULT = 1", nor(0, pull("Z", 1), 1)),
         ("Cat6 cut or shack off (no loop current)", "U3 LED off, KILL pulled to 1 by R34", "KILL = 1", nor(1, 0, 0)),
         ("Controller board unplugged from J14", "RLY_EN on the RF board Z, pulled to 0 by R3", "expanders in reset, +12V_SW off", pull("Z", 0)),
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    bias_ok &= ("U1001", str(3 + k)) in m and len(q) == 1 and rf_parts[q[0]][0] == "BSS138BK" and len(rr) == 1
check(bias_ok, "A1..A4_BIAS_EN = U1001 IO0_0..3, BSS138BK gate, 100k pull-down")
check(all(spare_low("U1001", pn) for pn in range(13, 21)), "U1001 IO1_0..7 (spare): each held low by 10k to GND in RN1001, RN1002 (D-121)")
p("\n| RLY_EN | U1001 | EN pin | BSS138 gate | Bias feed |\n|---|---|---|---|---|")
p("| 0 | reset: inputs | Z | 0 (pull-down) | off |")
p("| 1 | input (default) | Z | 0 | off |")
p("| 1 | output 0 | 0 | 0 | off |")
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p("| PTT loop 2 | Controller on J14 | +3V3 on controller | RLY_EN | TX_ANY / K0 gate | K0 contacts | Radio sees |\n|---|---|---|---|---|---|---|")
for ptt, plugged, v33, en in itertools.product((0, 1), (1, 0), (1, 0), (1, 0)):
    if not plugged and (v33 == 0 or en == 1): continue          # unplugged: controller side does not matter; RLY_EN then 0
    if plugged and v33 == 0 and en == 1: continue                 # no 3V3: gate cannot give RLY_EN = 1
    tx = (ptt if v33 else "Z") if plugged else "Z"
    g = pull(tx, 0)
    sees = ("TX row" if g else "RX row") + (" with row relays" if en else ", row relays off: open line")
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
